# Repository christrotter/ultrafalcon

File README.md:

# Ultrafalcon - when learning doesn't want to hold hands with success
Let's start with a question: 

`How do you model learning that is accompanied by 'perceived failure'?`

As a parent, I'm constantly trying to ingrain my kids with a love of learning.  In learning, we can show thankfulness for what we have, and it's a way we can grow in perseverance and patience.  Knowing that children innately copy their parents in many things, including mannerisms, how are they copying my response to failure?  Do they ever see me fail?

Well, internet: here, see me fail...

### This learning experience has been generously sponsored by...

...my thanks and gratitude!

## Sponsorship details
This came into being when PCBWay offered to sponsor an entire PCB + PCBA order in exchange for me writing up a review of my experience on my blog.  After all was said and done, they paid for $140USD of product/shipping, I paid $45CAD import duties.

While I've usually gone to JLCPCB, when someone offers you a PCB sponsorship, you try not to look that gift horse over too closely - PCB costs add up!

I had just finished and submitted the mk19-pcb rev1 order, so something else was needed.  The only project I had come up with but dismissed was an expanded 'Falcon' PCB...

## Falcon EC11
Casuanoob's [Falcon EC-11 PCB](https://github.com/Bastardkb/Charybdis-EC11) rather blew me away when I was looking around for ideas.  I saw it in passing on the BKB discord's showcase channel - an encoder surrounded by LEDs!  Super cool.  

I ordered a stack of them, intending to make them a staple in my builds.  And indeed, they were introduced in the mk15 - one on each half - and I doubled down on the mk17, with each half having two!  The mk19 was going to get the same treatment.

This is what you get with a Falcon, seen on the mk17 & mk15:

## Designing the Ultrafalcon
As with most creative ventures (_well, for me_), there was a certain amount of 'sky's the limit' paired with 'standing on the shoulders of giants'.

**What if you could have a giant clacky center button on your giant encoder wheel that's an LCD and surrounded by LEDs?**

So I sketched something up in Fusion360...

Immediate feedback was that I had used far too few LEDs.  The original Falcon has 12 - the first iteration of the Ultrafalcon had 18 - final has 30.  Still complaints about too few LEDs.  The internet community is always there to help.

'But why?', you ask...

1. Why not?
2. The existing Falcon uses a small-footprint EC11 encoder that frankly is not designed for huge wheels to be attached.
3. How cool is a button that's also an LCD screen??
4. Using a PER-series encoder wheel requires a PCB, so, "while I'm in there".

## JLCPCB & PCBWay
During this sponsorship trial I noted some of the benefits of choosing [PCBWay](https://www.pcbway.com) over [JLCPCB](https://www.jlcpcb.com) are...
- a lot more customization and options available (_e.g. 14 copper sizes, 15 board thicknesses, more colours, etc_)
- full "white glove" turnkey assembly (_they source the parts for you - just provide a BOM_)

There is obviously a cost to the variety of choice (_production lines are not cheap!_), but if you really just want nothing to do with figuring out which parts are in stock, backporting that to your design, and the back and forth - it's a very tempting value proposition.

Practically, however, it means you're paying (_this is my observation based on my use cases_) ~50% more at PCBWay.  Apples to apples, I compared the pricing:
- Cost to make pcb (_JLC vs. PCBWay_): $5 +shipping vs. $45 +shipping
- Cost to PCBA (_JLC vs. PCBWay_): $40 (no PER60 encoders) vs. $95 (_incl. PER60 encoders_)
- Total cost, all-in (_JLC vs. PCBWay_): **$120CAD vs. $245CAD** (_$145USD = $200CAD + $45CAD duties_) (_JLC total includes price for mouser.ca to ship me the PER60 encoders_)

Is `time=money` true for you?  Then maybe PCBWay makes more sense.  

A hindsight note is that if you are coming from experiences with JLCPCB, you will be very confused about the process at PCBWay.

JLC expects you to do a certain amount of legwork:
1. browse the parts catalogue, figure out what is in stock
2. add them to your local design tool
3. submit BOM (_before the parts go out of stock!_) (_BOM = bill of materials_)

Accordingly, JLC's parts inventory/selection is seemingly infinite.

PCBWay has taken a different approach:
1. add whatever parts you fancy to your BOM
2. submit BOM
3. PCBWay sources the part or its analogue

The challenge for JLC regulars is that you expect to find parts in their catalogue that just aren't there - simple things like RGB LEDs!  So rather than browsing, you literally just jam in the manufacturer part number to your BOM and go about your day.
e.g. `SW1,1,,PER60,Bourns,PER601-P117-N0015,tht`

Amusingly, I used JLC's catalogue to source many of my part numbers.

So, there are some warts with both processes, but frankly the outcome is you can create custom PCBs for what amounts to peanuts, enlarging the sphere of what you can accomplish creatively.  So even with some bumps along the road - you are enabled to reach into previously unattainable levels of craftsmanship and execution.  "The future is now." as they say.

## Kicad learnings
Without boring the casual reader, suffice to say that the discipline of electronics/PCB design is a lot more rigid than software work, so the process you have to follow is somewhat non-negotiable.

1. Supply all of your schematic symbols and PCB footprints.
2. Lay out your schematic.
3. Draw the PCB, meeting the manufacturer's [specifications](https://www.pcbway.com/pcb_prototype/PCB_assembly_Capabilities.html) for [tolerances](https://jlcpcb.com/capabilities/pcb-capabilities).
4. Export the necessary files for production.

*(click for higher resolution)*

No big deal, right?

Well.  Ok, so this was a huge learning curve.  But, once you get the hang of it - remembering that this is an established discipline, with a high googl-a-bility factor - it's just a matter of searching and gluing things together.

*(click for higher resolution)*

Some foreshadowing.  I initially had trouble sourcing the symbol/footprint of the LED pacakge, so ended up copying it from someone else who had successfully ordered with that design.

Can you spot the error?  Yeah, nobody else could, either.

## From Kicad to Fusion
Kicad has a super handy feature: `Export -> STEP file`

This provides you with a file you can directly import into Fusion 360, which means you can model around a real-life representation of your PCB, including all the components like connectors, LEDs, encoder wheels, etc.  Pictured is a work-in-progress view of the "LCD screen button" design.

Refactoring the mk19 model thankfully wasn't too bad - there was just enough room for the new PCB size.

## The order
My particular needs for the Ultrafalcon required the Bourns PER60 encoder, unfortunately only available via US sources.  This required an additional two to three weeks of processing time on their end - order the part from the US to China, get it on the bench, manually solder in place - and the parts themselves are $10CAD a piece.

When I mentioned warts earlier, this is where a particular oddity comes into play.  After submitting the parts and the engineering department finally gets to auditing them, the BOM I submitted is transformed into an XLS spreadsheet on their end.  They make some adjustments and send it over to me - via email - and I have to open the file, add my comments, save, and re-email it to them.

This is very very strange given the high levels of automation everywhere else on their site.

But, it worked out okay, after I went through the rigamarole of importing the XLS into Google Sheets.

Both JLCPCB and PCBWay require some level of your effort!

### Timing
Worth calling out first that adding US-source-only components definitely slowed things down, but, it's good info:
- Jan 25 - order submitted in full
- Feb 27 - order received at my house

A 30-ish day cycle time on figuring out 'will my design actually work' is a good reality check compared to the software world of 'minutes or less'.

## Receiving day

Once the order was processed, PCBWay shipped it via DHL and it arrived within a week (_speaking of 'the future is now' - shipping around the globe in less than a week?_).  Packaging is impressive - everything is static-bagged and generously enfolded in bubble-wrap.

## Testing
There's another important distinction I learned between the two: 
- JLC will take your files as-is and build _whatever you have provided_.  
- PCBWay will _correct any errors behind the scenes_ to ensure maximum quality.  

This seems as if PCBWay is doing you a favour, but if you combine inexperience, "it worked over there, probably be fine over here" attitude, and silent mistake fixing, you get... **a non-functional board**.

After all of the work, waiting, and planning - something had gone wrong!

When supplying power/gnd to the board, it would rapidly try to emulate a space heater - not something I'd designed in!

Thanks to an ancient 30x pocket scope, the trusty `burkfers` and `GeorgeN`, and a datasheet, the issue quickly became clear: the LEDs were mounted 90-degrees clockwise from what my PCB diagram required.

Still more to be gleaned from this prototype, however!!

### Testing the lug assemblies

A head scratcher - not sure how this happened...but obviously some Fusion fixes to be done.  This is the 'lower lug' of the connector.

### We can test the fitment of the pcb to the case

Aha!  I undersized the print.  When we do Ultrafalcon rev2, we can shrink the pcb to fit.  Visually, the size of it is pleasing.  Chomnky.

### And how does it feel?
Very happy with the PER60's size.  It's a little stiff, but with use that should ease up.  The general wheel size - 85mm - is great, an improvement on the mk17's 57mm.  This prototype is missing the LED reflector/diffusers.

# Conclusion - Lessons learned and next steps
Not all learning is accompanied by "traditional" success.  But all learning is a success in and of itself.

- Sometimes you can do everything you know to be right and still 'fail'; revelation that you still have more to know, more to learn - this is ok!
- As in so many cases, even in the same industy niche you can have very different paradigms surrounding 'accomplish the goal'; don't assume that what works for NicheCompanyA will work for NicheCompanyB.
- Corollary for the above: You can't know when you've missed something, so design slack into the system.

How do you model "learning through failure" to our colleagues?  Our peers?  Our families?  Our communities?

I got the opportunity to show my children that even daddy fails at new things, and this is okay!  I learned from it!

What's next?

Why, Ultrafalcon rev2, of course! 

# Addendum - PCB details
With this PCB you get...
- [Bourns PER60 encoder w. debounce circuit](https://www.mouser.ca/new/bourns/bourns-per60-incremental-ring-encoders/)
- MX switch cutout (_or, passthrough for whatever else you mount in the middle_)
- Fitment for large 77mm or larger encoder handwheel
- 30 programmable SK6805-ER15 LEDs (_e.g. use with QMK's rgb matrix_) w. LED signal passthrough (_DI and DO pins_)
  - 24 on the outside of the encoder (_b/c 24 is twice 12...?_)
  - 6 on the inside of the encoder (_b/c two rings of illumination are better than one?_)
- 330ohm resistor on the DI line (datasheet recommendation)
- 1uF capacitor (_help avoid capacitance_)
- JST-XH 2.54 footprint (_or, just 8 through-holes spaced at 2.54mm_)

TODO: Also included are the relevant STL and Fusion files to get you started on including this in your build.

# Addendum - Using the Ultrafalcon in your own design
Open-source, use however you want - though really of most utility to the keyboard community.

## Mounting to your shell
My current method is to use a static "interface" part that gets combined into the forms shell.  Then the rest of your important pieces locate onto the "interface" part and everything works out swell.  Usually.

# not-included-in-the-PCB-details
I'll be using a GC9A01 circular 1.28" TFT and QMK's quantum painter feature.  The TFT uses an 8-pin 0.5mm pitch FPC cable which I'm threading down into the keyboard base.

# PCB details

The goal of this design was to provide a larger encoder wheel experience, and while doing that, why not add more LEDs? ... annnd while doing that, maybe add the capability of "room for activities" inside the encoder wheel.

Some of the existing Falcon issues I have are mostly centered on the fact that the EC-11 package was never meant to mount a super huge wheel, so you get wobble and tilt, and it generally just feels not quite right.  Further, the pcb was designed to fit the wonderful Charybdis keyboard, so has some packaging constraints that are unfortunate when not using a Charybdis! (_e.g. pin headers not on same axis_)

There's also no debounce as-is, though I'm sure something could be added.  The software debounce helps but you still run into issues from time to time.

So, being new to pcb design, I gave it a shot.
- dual ground planes (_2-layer board_)
- via 'ties' to keep ground as contiguous as possible
- 0.4mm power traces / 0.25mm data traces
- avoiding running power/data together as much as possible
- datasheets provide the source of design truth
- capacitor on-board to help with capacitance issues
- M3 mounting holes w. plating
- MX-size cutout (_plus another cutout for FPC cable/mounting block locator_)

# Schematic
- PER60 debounce circuit
  - 4x 10k ohm resistors
  - 2x 0.01uF capacitors
- 1uF capacitor for LED supply
- 330 ohm resistor for LED DI pin
- NOTE: to use the MX switch, solder some wires to the pins of the MX switch and the SW_A & SW_B pins; that pair of pins links up with the SW_A & SW_B pins on the 8-pin JST connection

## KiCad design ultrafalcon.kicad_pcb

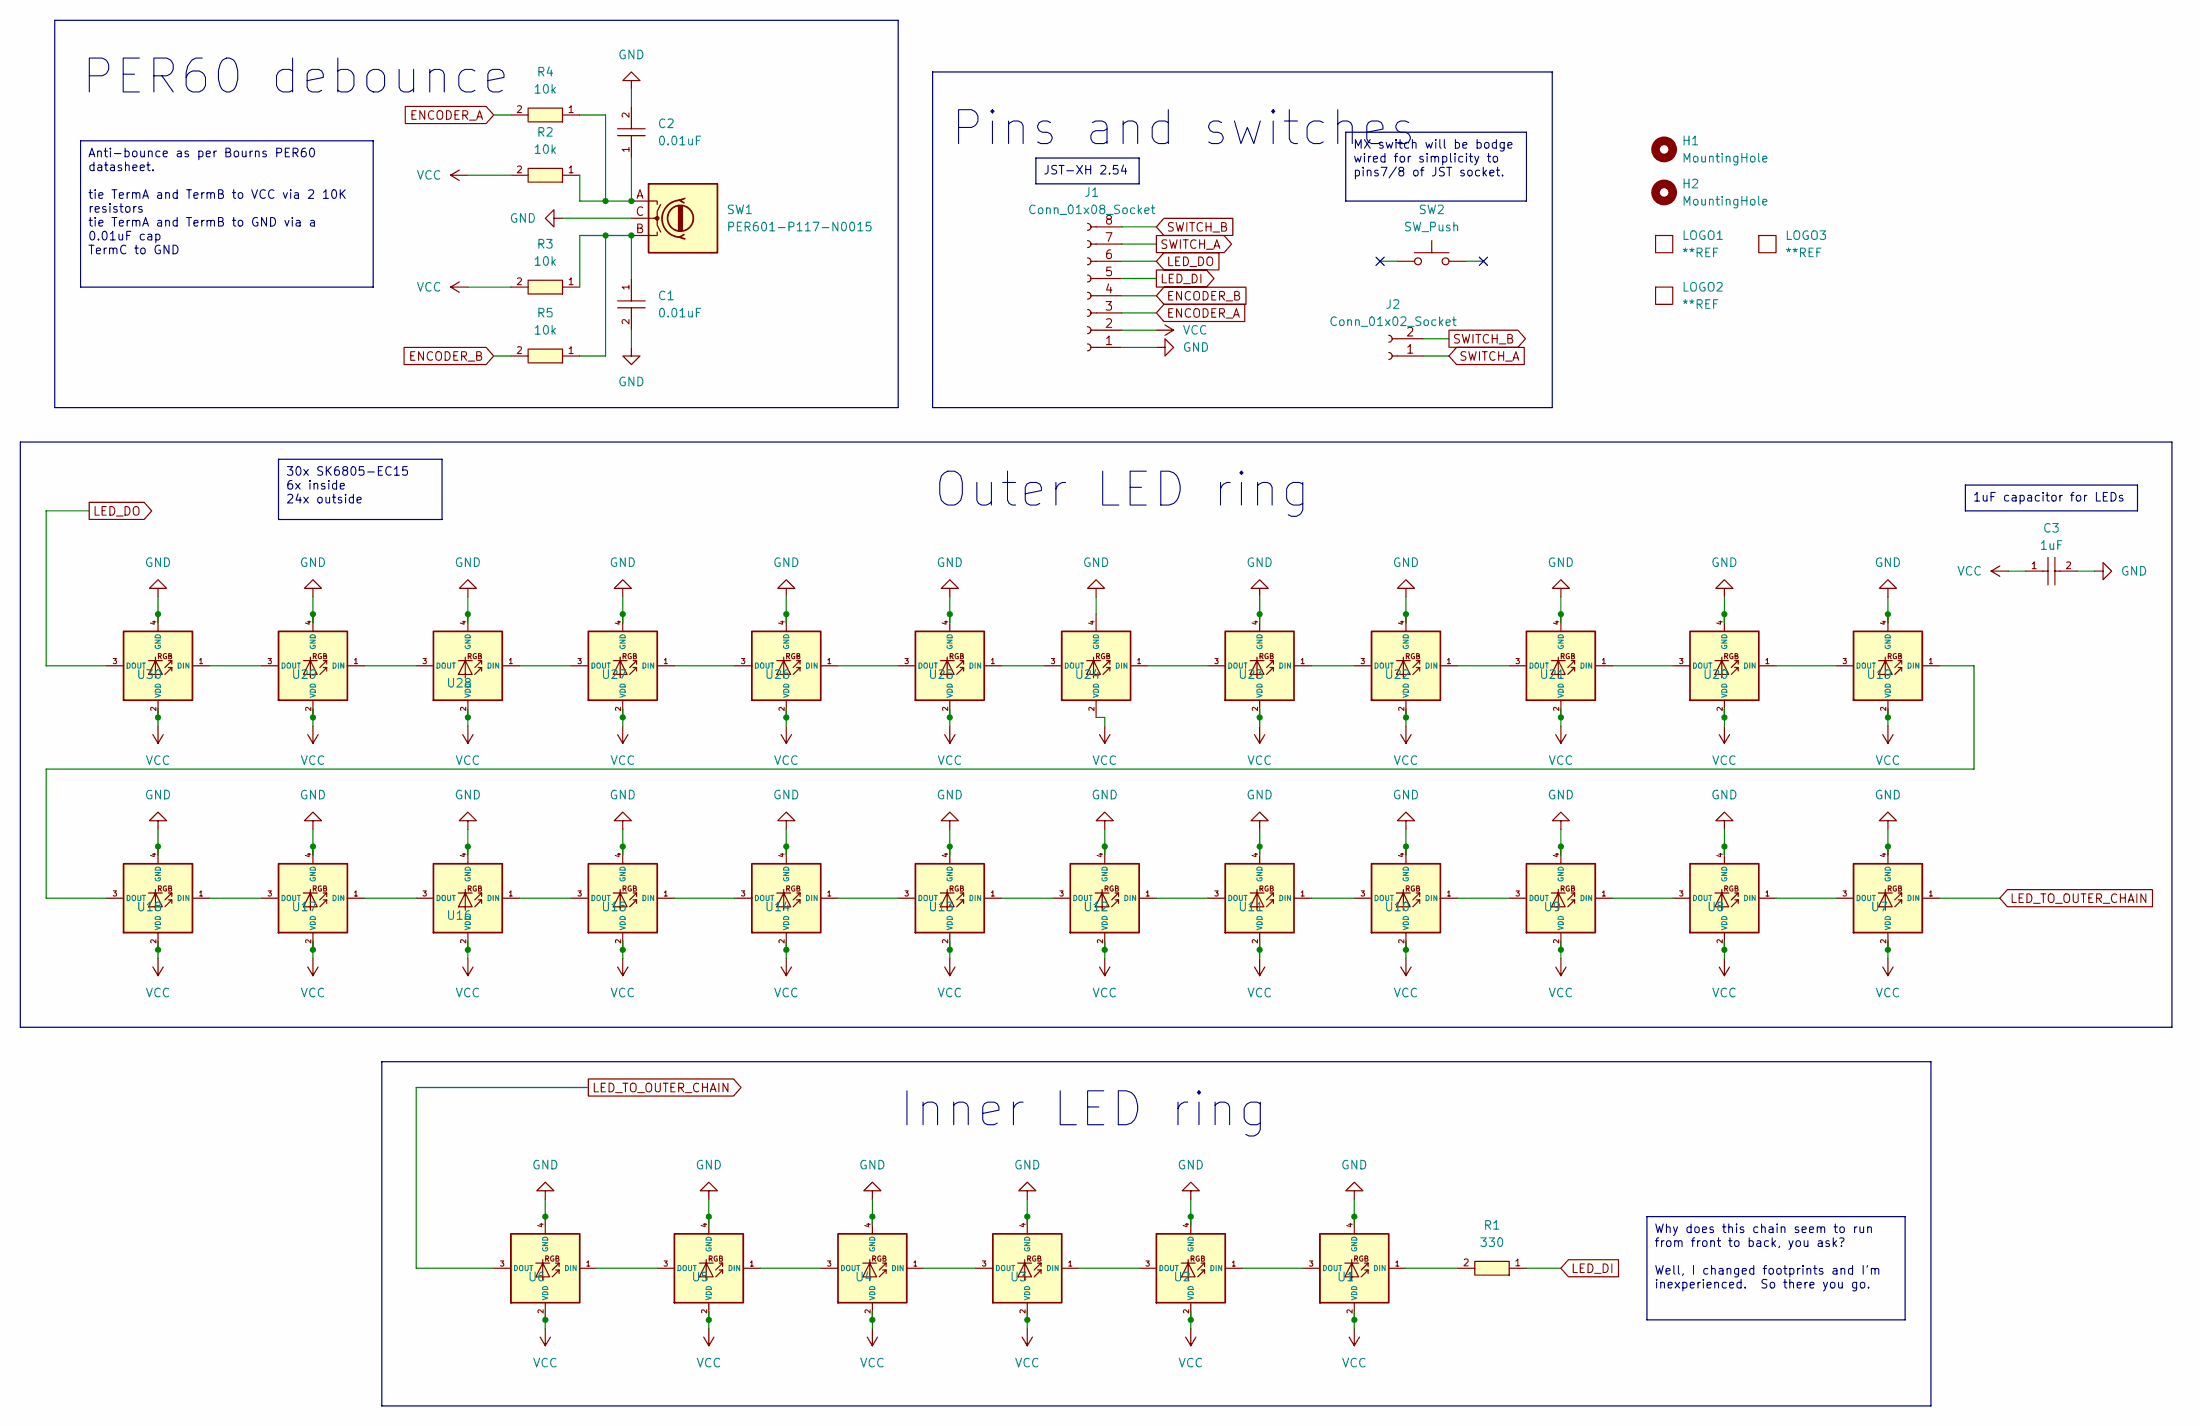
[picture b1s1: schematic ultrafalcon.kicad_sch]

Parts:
C1, C2: 0.01uF; C0402; LCSC C1525
C3: 1uF; C0402; LCSC C1525
H1, H2: MountingHole; MountingHole_3.2mm_M3_Pad_Via
J1: Conn_01x08_Socket; JST_EH_B8B-EH-A_1x08_P2.50mm_Vertical
J2: Conn_01x02_Socket; PinHeader_1x02_P2.54mm_Vertical
LOGO1: **REF; awesome-logo
LOGO2: **REF; pcbway-logo-neg40mm
LOGO3: **REF; ultrafalcon-qr-15mm
R1: 330; R0603; LCSC C23138
R2, R3, R4, R5: 10k; R0603; LCSC C23138
SW1: PER601-P117-N0015; PER60
SW2: SW_Push; SW_MX_cutout
U1, U2, U3, U4, U5, U6, U7, U8, U9, U10, U11, U12, U13, U14, U15, U16, U17, U18, U19, U20, U21, U22, U23, U24, U25, U26, U27, U28, U29, U30: SK6805-EC15; LED_dilemma_SK6805-EC15_1.5x1.5mm_P0.6mm_handsolder; MPN SK6805-EC15; LCSC C2890035

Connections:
ENCODER_A: J1.3, R4.2
ENCODER_B: J1.4, R5.2
GND: C1.2, C2.2, C3.2, J1.1, SW1.C, U1.4 (GND), U2.4 (GND), U3.4 (GND), U4.4 (GND), U5.4 (GND), U6.4 (GND), U7.4 (GND), U8.4 (GND), U9.4 (GND), U10.4 (GND), U11.4 (GND), U12.4 (GND), U13.4 (GND), U14.4 (GND), U15.4 (GND), U16.4 (GND), U17.4 (GND), U18.4 (GND), U19.4 (GND), U20.4 (GND), U21.4 (GND), U22.4 (GND), U23.4 (GND), U24.4 (GND), U25.4 (GND), U26.4 (GND), U27.4 (GND), U28.4 (GND), U29.4 (GND), U30.4 (GND)
LED_DI: J1.5, R1.1
LED_DO: J1.6, U30.3 (DOUT)
LED_TO_OUTER_CHAIN: U6.3 (DOUT), U7.1 (DIN)
unnamed: C1.1, R3.1, R5.1, SW1.B
unnamed: C2.1, R2.1, R4.1, SW1.A
unnamed: R1.2, U1.1 (DIN)
unnamed: U1.3 (DOUT), U2.1 (DIN)
unnamed: U2.3 (DOUT), U3.1 (DIN)
unnamed: U3.3 (DOUT), U4.1 (DIN)
unnamed: U4.3 (DOUT), U5.1 (DIN)
unnamed: U5.3 (DOUT), U6.1 (DIN)
unnamed: U7.3 (DOUT), U8.1 (DIN)
unnamed: U8.3 (DOUT), U9.1 (DIN)
unnamed: U9.3 (DOUT), U10.1 (DIN)
unnamed: U10.3 (DOUT), U11.1 (DIN)
unnamed: U11.3 (DOUT), U12.1 (DIN)
unnamed: U12.3 (DOUT), U13.1 (DIN)
unnamed: U13.3 (DOUT), U14.1 (DIN)
unnamed: U14.3 (DOUT), U15.1 (DIN)
unnamed: U15.3 (DOUT), U16.1 (DIN)
unnamed: U16.3 (DOUT), U17.1 (DIN)
unnamed: U17.3 (DOUT), U18.1 (DIN)
unnamed: U18.3 (DOUT), U19.1 (DIN)
unnamed: U19.3 (DOUT), U20.1 (DIN)
unnamed: U20.3 (DOUT), U21.1 (DIN)
unnamed: U21.3 (DOUT), U22.1 (DIN)
unnamed: U22.3 (DOUT), U23.1 (DIN)
unnamed: U23.3 (DOUT), U24.1 (DIN)
unnamed: U24.3 (DOUT), U25.1 (DIN)
unnamed: U25.3 (DOUT), U26.1 (DIN)
unnamed: U26.3 (DOUT), U27.1 (DIN)
unnamed: U27.3 (DOUT), U28.1 (DIN)
unnamed: U28.3 (DOUT), U29.1 (DIN)
unnamed: U29.3 (DOUT), U30.1 (DIN)
SWITCH_A: J1.7, J2.1
SWITCH_B: J1.8, J2.2
VCC: C3.1, J1.2, R2.2, R3.2, U1.2 (VDD), U2.2 (VDD), U3.2 (VDD), U4.2 (VDD), U5.2 (VDD), U6.2 (VDD), U7.2 (VDD), U8.2 (VDD), U9.2 (VDD), U10.2 (VDD), U11.2 (VDD), U12.2 (VDD), U13.2 (VDD), U14.2 (VDD), U15.2 (VDD), U16.2 (VDD), U17.2 (VDD), U18.2 (VDD), U19.2 (VDD), U20.2 (VDD), U21.2 (VDD), U22.2 (VDD), U23.2 (VDD), U24.2 (VDD), U25.2 (VDD), U26.2 (VDD), U27.2 (VDD), U28.2 (VDD), U29.2 (VDD), U30.2 (VDD)

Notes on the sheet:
1uF capacitor for LEDs
Anti-bounce as per Bourns PER60 datasheet. tie TermA and TermB to VCC via 2 10K resistors tie TermA and TermB to GND via a 0.01uF cap TermC to GND
MX switch will be bodge wired for simplicity to pins7/8 of JST socket.
Why does this chain seem to run from front to back, you ask? Well, I changed footprints and I'm inexperienced. So there you go.
30x SK6805-EC15 6x inside 24x outside
JST-XH 2.54
Inner LED ring
Pins and switches
PER60 debounce
Outer LED ring

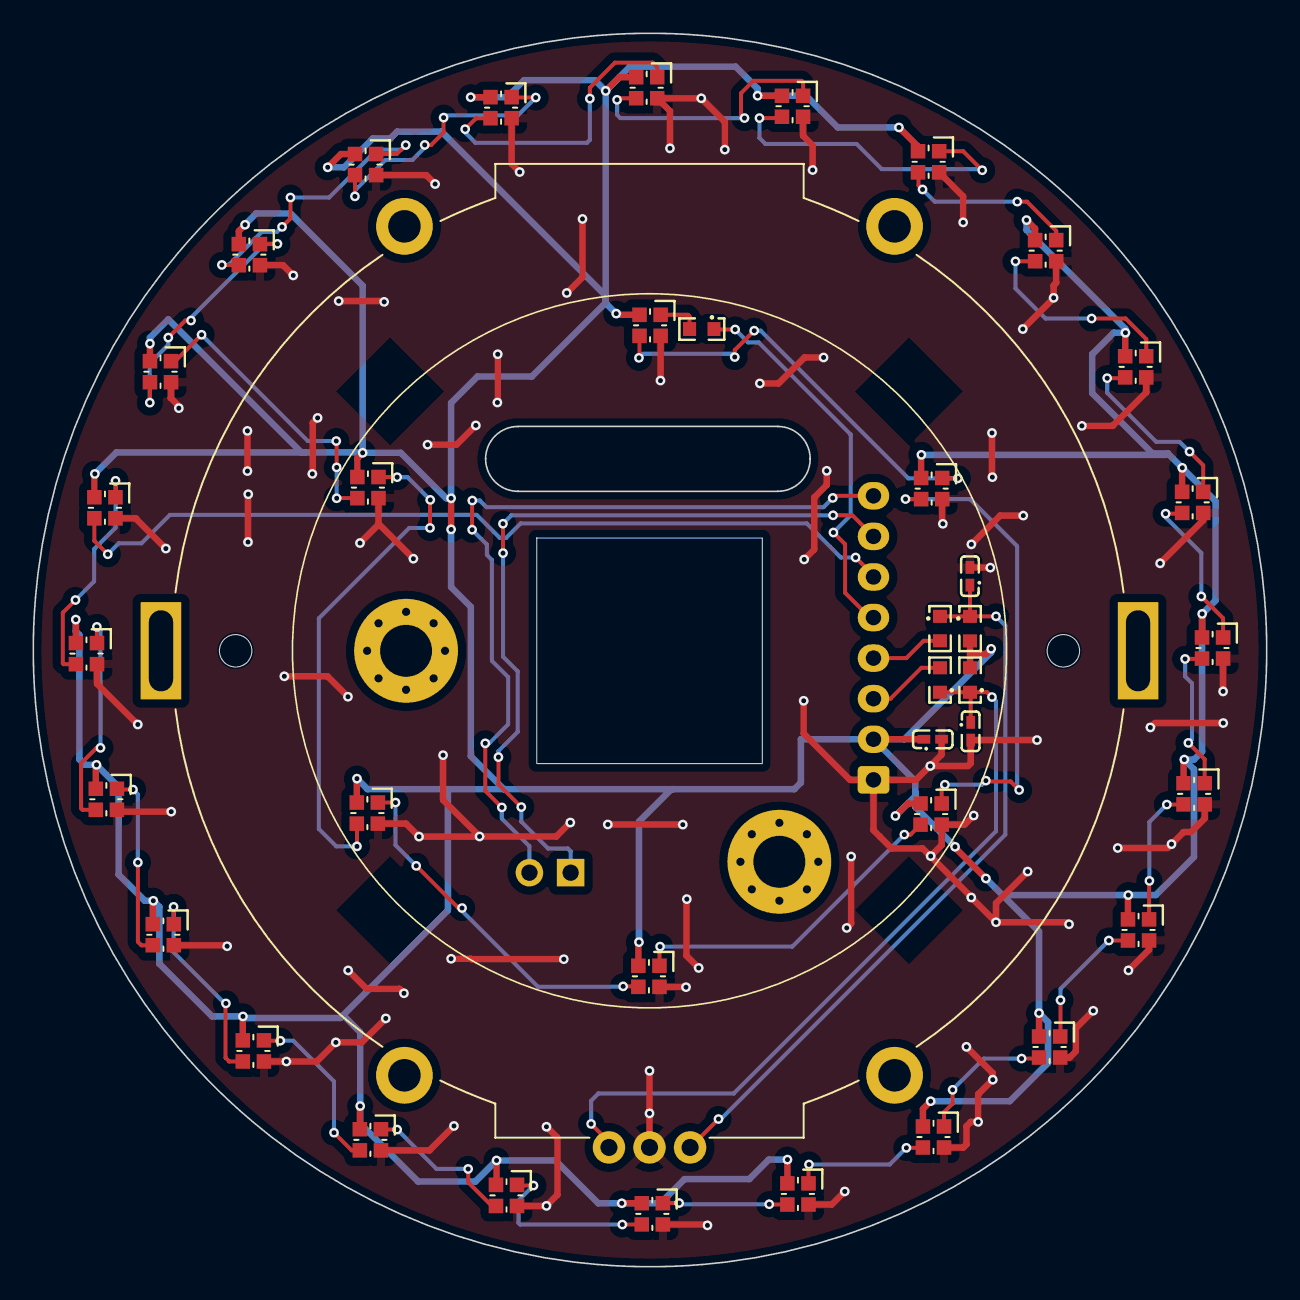
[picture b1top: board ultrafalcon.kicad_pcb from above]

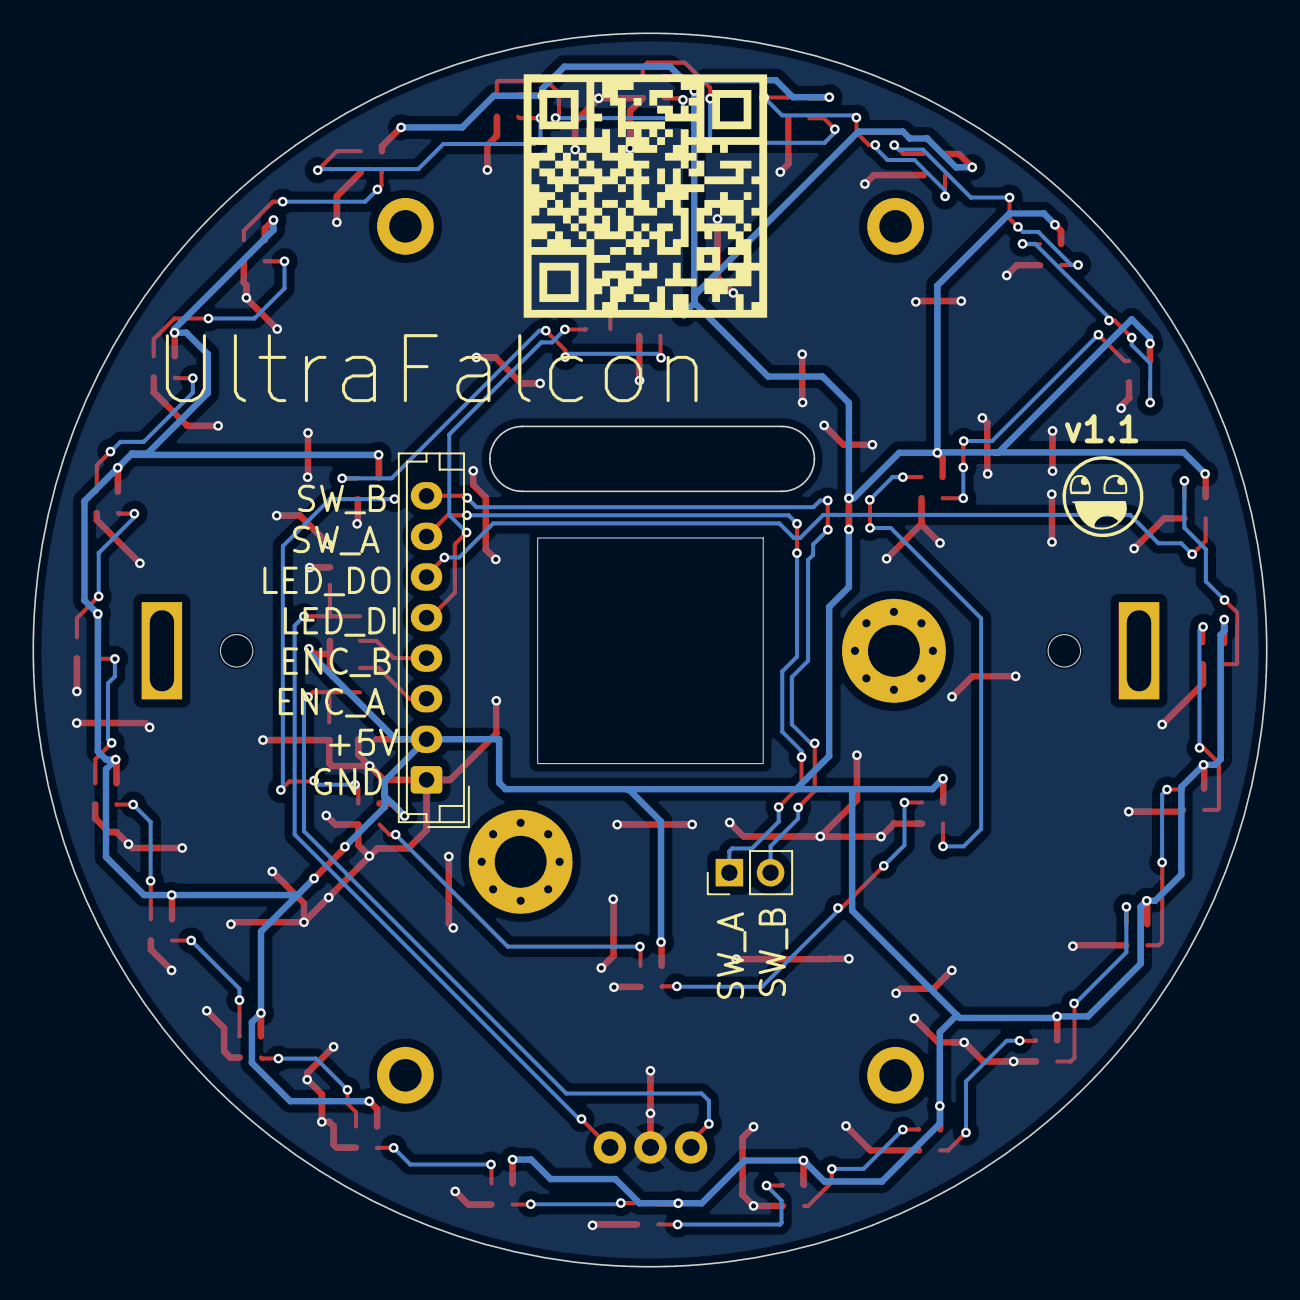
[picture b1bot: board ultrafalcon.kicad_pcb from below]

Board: 2 copper layers, 76.0 x 76.0 mm, 46 parts (4 on the bottom side), 40 nets.

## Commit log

2024-01-14 getting initial ideas down for testing in fusion
2024-01-18 jan17 updates
2024-01-19 ready for first review
2024-01-19 adding better notes
2024-01-19 replacing the led footprint and symbol, doing the tracing
2024-01-19 moving text around, adding rear labels, updating footprints
2024-01-22 getting the board ready for pcbway
2024-01-22 jan22 updates, almost ready for production
2024-01-22 updating the pictures and schematic to match new pins
2024-01-22 fixing some trace spacing
2024-01-23 final changes before submitting
2024-02-28 updating readme and images
2024-02-29 fixed the incorrect footprint silkscreen
2024-02-29 missed a silkscreen change
